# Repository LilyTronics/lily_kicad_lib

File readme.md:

# Lily KiCad Library

This is a free to use KiCad library.

Compatible with the latest release of KiCad (no backwards compatibility)

* More than 400 symbols and 80 footprints.
* Datasheet for each part (if applicable)
* 3D models for each footprint (if applicable)
* Lily KiCad toolbox:
  * Check library for consistency
  * Generate part IDs for the Lily ERP system
  * Generate manufacturing data for a design
    * PDF files for documentation (schematics and component placement)
    * Import for the Lily ERP
    * Bill of materials (BOM) for Excell
    * BOM for JLCPCB (with specific JLCPCB part IDs)
    * Gerbers and drill files
    * Position file for JLCPCB (can also be used for other manufacturers)
    * ODB+ output
    * 3D model of PCB
    * Archive design after generating output for traceability

Additional information:

* [Overview of all symbols and footprints](https://lilytronics.github.io/lily_kicad_lib/library_report.html)
* [Setup KiCad using this repo](docs/setup_kicad.md)

Do you have a request for a component? Submit a request using the [issue tracker](https://github.com/LilyTronics/lily_kicad_lib/issues).
Please specify a specific manufacturer, manufacturer part ID if possible.

## Setup

The repo is set up as follows:

```
lily_kicad_lib/
  |- 3d_models                  # 3D models for the footprints
  |- docs                       # documentation, datasheets, source for the GitHub pages
  |- lily_footprints.pretty     # footprint library
  |- projects                   # example and test projects
  |- symbols                    # symbols library
  |- templates                  # design templates, sheet templates, etc
  |- toolbox                    # sources of the Lily KiCad toolbox, with build script for build an executable
```

### 3D models

The 3D models are taken from three sources:

* KiCad 3D models
* Manufacturer 3D models
* Self created 3D models (design is included in the repo)

### Footprints

Footprints are created using the specifications of the manufacturers.
All footprints have a 3D model attached if applicable.
All footprints have the following extra attributes:

* Revision: numeric value for the revision of the footprint.

### Symbols

All symbols have the following extra attributes:

* Revision: numeric value for the revision of the symbol.
* Status: Active or Obsolete
* Manufacturer: manufacturer name (original, alternatives are not added)
* Manufacturer_ID: manufacturer part ID (original, alternatives are not added)
* Lily_ID: part ID for the ERP system used in LilyTronics.
* JLCPCB_ID: part ID used by JLCPCB.

## Usage

There are two ways you can use the KiCad libraries:

* As a project specific library
* As a global library

Which one you choose is depending on your preferred way of working. See the KiCad documentation on how to add libraries.
If your KiCad project is also in a git repository, you can clone this library as a sub module in your git poject.
See the Git documentation on how to add sub modules to your projects.

## Disclamer

This library is provided as is, without any support.
We do not take any liability for damages when using this library.

(c) LilyTronics (https://lilytronics.nl)

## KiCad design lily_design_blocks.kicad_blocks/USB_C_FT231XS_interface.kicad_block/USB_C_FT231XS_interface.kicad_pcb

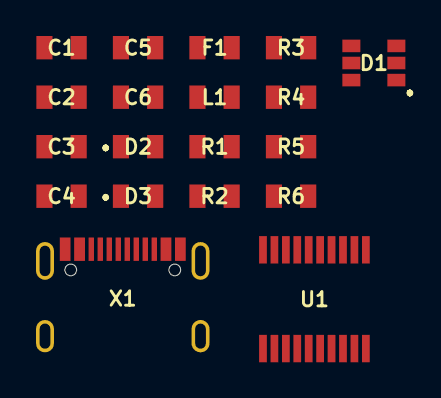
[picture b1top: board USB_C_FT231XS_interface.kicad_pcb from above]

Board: 2 copper layers, 19 parts (0 on the bottom side), 15 nets, no tracks yet.

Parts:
C1: 10n; cap_0805
C2, C6: 100n; cap_0805
C3, C5: 47p; cap_0805
C4: 4u7; cap_0805
D1: SRV05-4; sot23-6_sc74
D2, D3: green; led_0805
F1: 0.35A/0.75A; fuse_ptc_0805
L1: 600R/2A; ind_0805
R1, R2: 5k1; res_0805
R3, R4: 27R; res_0805
R5, R6: 470R; res_0805
U1: FT231XS; ssop20_pitch25_341x154mil
X1: usb_c; con_usb_c_receptacle_16p

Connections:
GND: C1.2, C2.2, C3.2, C4.2, C5.2, C6.2, D1.2 (GND), R1.2, R2.2, U1.6 (GND), U1.16 (GND), X1.1 (SH), X1.A1 (GND), X1.A12 (GND), X1.B1 (GND), X1.B12 (GND)
unnamed: C5.1, D1.1 (CH1), D1.3 (CH2), R4.2, X1.A7 (D-), X1.B7 (D-)
unnamed: C3.1, D1.4 (CH3), D1.6 (CH4), R3.2, X1.A6 (D+), X1.B6 (D+)
unnamed: C1.1, D1.5 (VCC), F1.2, L1.1
unnamed: C6.1, D2.2 (A), D3.2 (A), U1.3 (VCCIO), U1.13 (3V3), U1.14 (~RESET)
unnamed: D2.1 (K), R5.1
unnamed: D3.1 (K), R6.1
unnamed: F1.1, X1.A4 (VBUS), X1.A9 (VBUS), X1.B4 (VBUS), X1.B9 (VBUS)
unnamed: R5.2, U1.17 (CBUS1)
unnamed: R6.2, U1.10 (CBUS2)
unnamed: R3.1, U1.11 (D+)
unnamed: R4.1, U1.12 (D-)
unnamed: C2.1, C4.1, L1.2, U1.15 (VCC)
unnamed: R2.1, X1.A5 (CC1)
unnamed: R1.1, X1.B5 (CC2)

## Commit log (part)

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2026-01-13 updated capacitors test project
2026-01-13 updated documentation symbols project
2026-01-13 add LORA module RFM95W
2026-01-13 updated power symbols test project
2026-01-13 updated transistors test project
2026-01-13 updated various components test project
2026-01-13 updated potentiometers test project
2026-01-13 renamed datasheet
2026-01-13 updated fuses test project
2026-01-13 updated inductors test project
2026-01-13 refactor projects checker work in progress
2026-01-13 updated resistors test project
2026-01-13 updated switches test project
2026-01-13 updated ic test project
2026-01-13 Updated library report
2026-01-13 file renamed
2026-01-14 add battery charger BQ24073 in VQFM-16
2026-01-16 add JST 3 pin connector
2026-01-16 Update footprint count
2026-01-19 add ESP-C6-MINI-1 module
2026-01-20 updated ESP-C6-MINI-1 symbol
2026-01-20 add SMA right angle connector
2026-01-23 add unused items checker checks for unused datasheets
2026-01-23 add check fro unused foorptints
2026-01-23 add check for unused 3D models
2026-01-28 updated thermal reliefs
2026-01-28 add check for unused symbols
2026-01-28 add check for not matching pictures
2026-01-28 add unused items check to the toolbox
2026-01-28 archived unused symbols and footprints
2026-01-28 removed debug print
2026-01-28 removed old todo list
2026-01-29 remove pycharm and venv in git ignore
2026-01-29 updated test projects
2026-01-29 make exception for TC2030-IDC connector
2026-01-29 updated value of the TC2030 connector
2026-01-29 add test project for PCB footprints only
2026-02-02 removed old field from footprint
2026-02-02 fix handling missing extends property
2026-02-02 fix handling missing model property
2026-02-02 do not make fields equal between all footprints, makes the checks more accurate
2026-02-02 do not make fields equal between symbols, makes the checker more accurate
2026-02-02 add check footprints on missing fields (wip)
2026-02-03 removed footprint property (no longer in V9)
2026-02-03 removed commented code
2026-02-03 add check footprint properties (wip)
2026-02-03 fix reading all attributes for the properties
2026-02-03 fix handling the extends property
2026-02-03 move project checker to checker package
2026-02-03 updated fields
2026-02-03 fix erp check filter to latest library updates
2026-02-03 fix handling optional fields
2026-02-03 add check for symbols vs footprints
2026-02-03 build toolbox V3.17
2026-02-03 updated report messages
2026-05-18 add AT42QT1010 touch sensor IC
2026-05-20 fixed import
2026-05-20 build toolbox V3.18
2026-05-20 updated minor issues in library
2026-05-20 fixed some checks
2026-05-20 build toolbox V3.19
2026-05-20 fix properties check for switches
2026-05-21 build toolbox V3.20
2026-05-21 don't include dnp components in BOM
2026-05-22 update properties
2026-05-22 add AT24QT1010 to test design
2026-05-24 build toolbox V3.21
2026-05-24 updated design
2026-05-24 fixed log messages
2026-05-24 add design block for USB-C FT231XS schematics
2026-05-24 add multi channel test project
2026-05-24 improved handling multi instance symbols (multi channel, design blocks)
2026-05-24 fix pinout for USB D+ and D-
2026-05-24 remove commented code
2026-05-24 fixed check for value
2026-05-24 removed duplicate code
2026-05-24 fix multisheet design
2026-05-24 update PCB for multi channel
